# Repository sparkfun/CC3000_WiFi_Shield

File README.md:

CC3000_WiFi_Shield
====================

[  
*CC3000 WiFi Shield (WRL-12071)*](https://www.sparkfun.com/products/12071)

Arduino WiFi shield for the [TI CC3000 module](http://www.ti.com/product/cc3000). The datasheet can be found [here](http://www.ti.com/lit/ds/symlink/cc3000.pdf).

Arduino library and examples can be found in the [SFE_CC3000_Library](https://github.com/sparkfun/SFE_CC3000_Library).

This part was created in Eagle v6.5.0. Example sketches were created in Arduino v1.0.5.

Repository Contents
-------------------

* **/Hardware** - All Eagle design files (.brd, .sch, .STL)
* **/Production** - Test bed files and production panel files

Version History
---------------
* **v1.0** Initial release

License Information
-------------------
The hardware is released under [Creative Commons Share-alike 3.0](http://creativecommons.org/licenses/by-sa/3.0/).  
All other code is open source so please feel free to do anything you want with it; you buy me a beer if you use this and we meet someday ([Beerware license](http://en.wikipedia.org/wiki/Beerware)).

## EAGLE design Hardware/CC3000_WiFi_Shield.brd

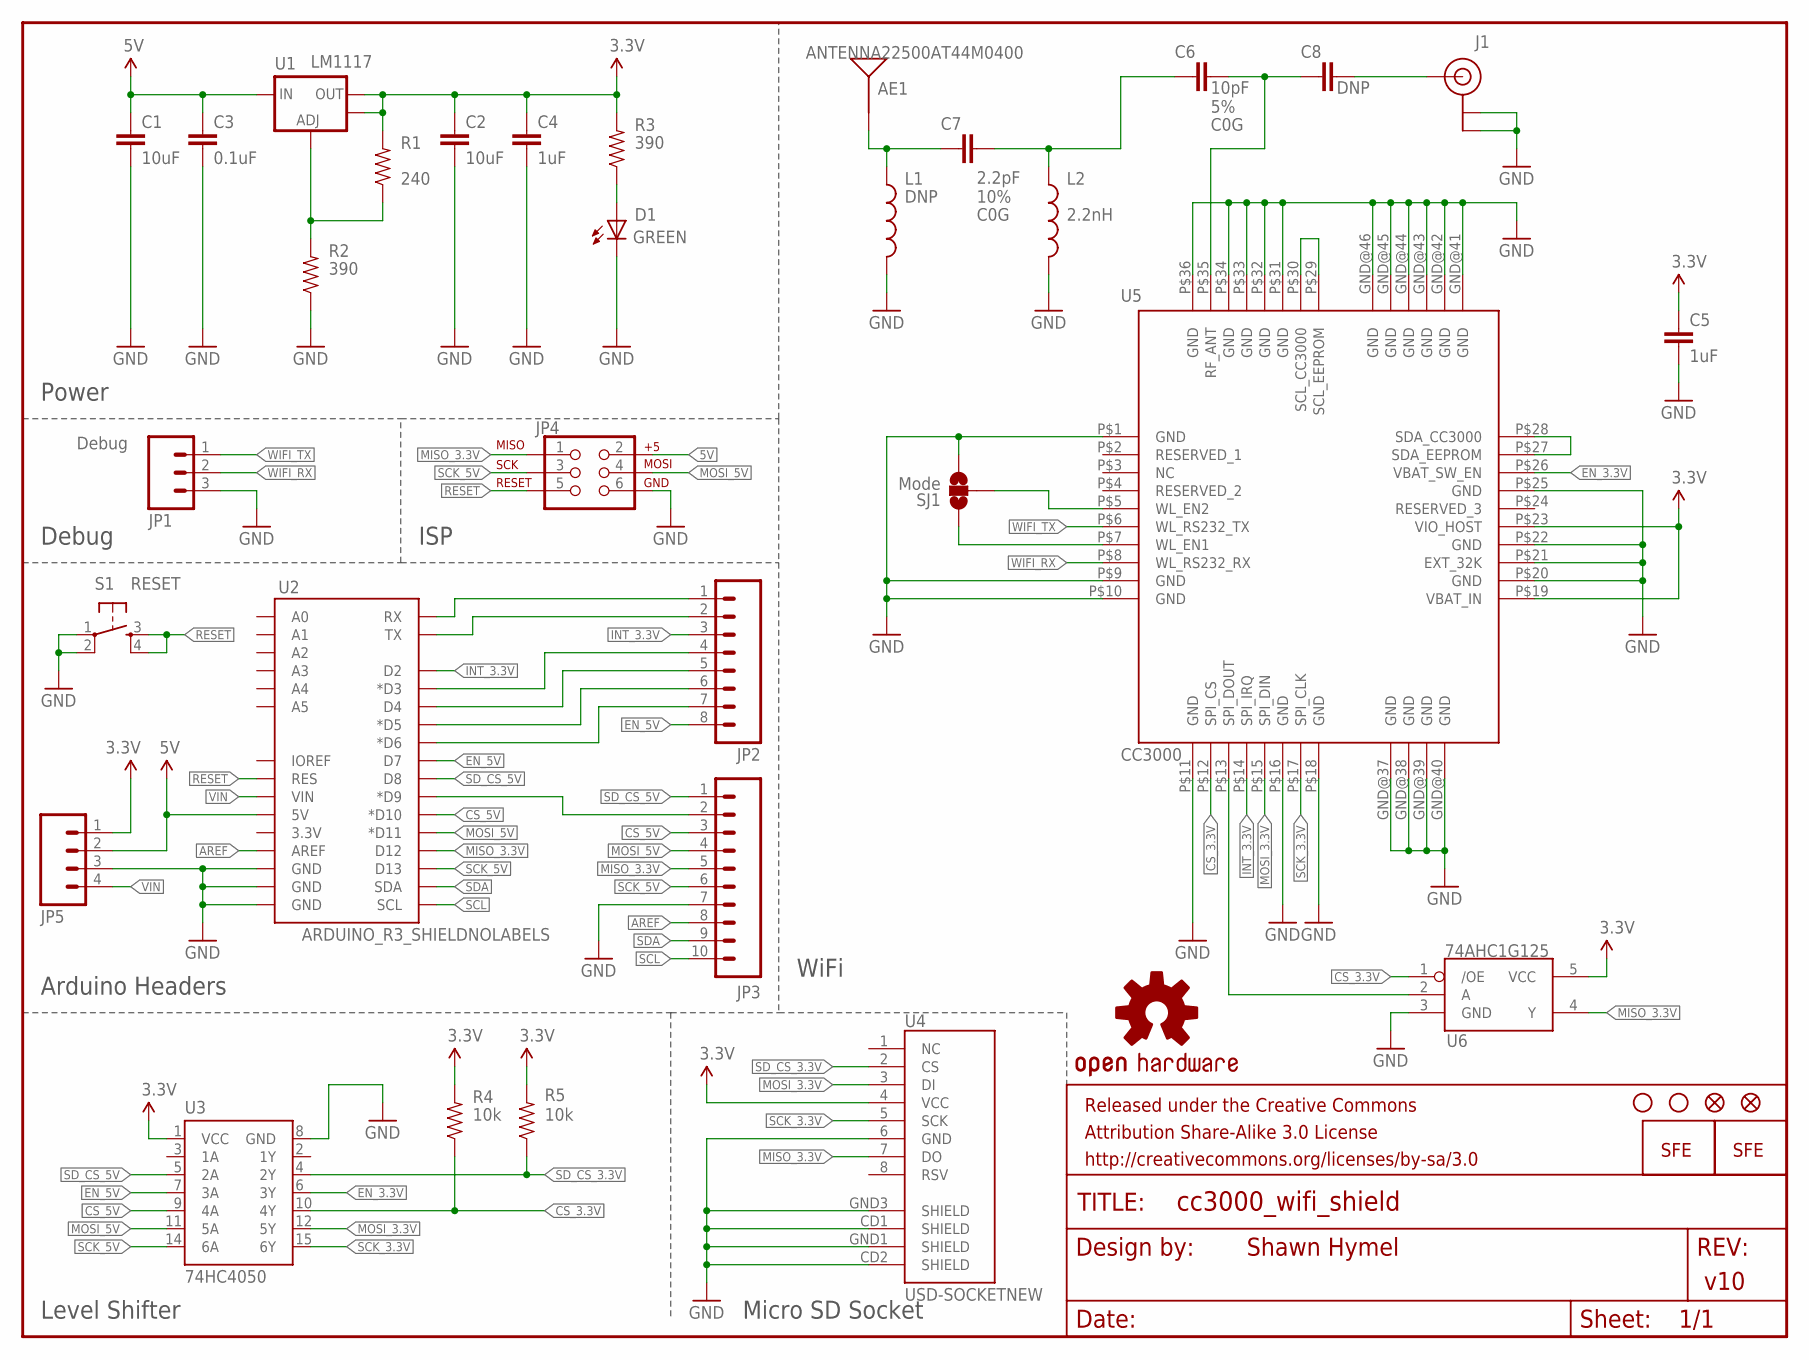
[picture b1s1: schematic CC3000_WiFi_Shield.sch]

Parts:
AE1: ANTENNA22500AT44M0400; ANTENNA-CHIP_2500AT44M0400
C1, C2: 10uF; 0805
C3: 0.1uF; 0603-CAP
C4, C5: 1uF; 0805
C6: 10pF; 0603-CAP
C7: 2.2pF; 0603-CAP
C8: DNP; 0603-CAP
D1: GREEN; LED-0603
FID1, FID2: FIDUCIAL1X2; FIDUCIAL-1X2
FRAME1: FRAME-LETTER; CREATIVE_COMMONS
J1: U.FL
JP1: Debug; 1X03
JP2: M08NO_SILK; 1X08_NO_SILK
JP3: M10NO_SILK; 1X10_NO_SILK
JP4: AVR_SPI_PRG_6PTH; 2X3
JP5: M04PTH; 1X04
L1: DNP; 0603
L2: 2.2nH; 0603
LOGO1: OSHW-LOGOS; OSHW-LOGO-S
LOGO2: LOGO-SFENEW; SFE-NEW-WEBLOGO
LOGO3: LOGO-SFESK; SFE-LOGO-FLAME
R1: 240; 0603-RES
R2, R3: 390; 0603-RES
R4, R5: 10k; 0603-RES
S1: RESET; TACTILE_SWITCH_SMD
SJ1: Mode; SJ_3_PASTE1&2
STANDOFF1, STANDOFF2: STAND-OFF
U1: LM1117; SOT223
U2: ARDUINO_R3_SHIELDNOLABELS; UNO_R3_SHIELD_NOLABELS
U3: 74HC4050; SO016
U4: USD-SOCKETNEW; MICRO-SD-SOCKET-PP
U5: CC3000; QFN-46_CC3000
U6: 74AHC1G125; SOT23-5

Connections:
3.3V: C2.1, C4.1, C5.1, JP5.1, R1.2, R3.2, R4.2, R5.2, U1.2 (OUT), U1.4 (OUT), U3.1 (VCC), U4.4 (VCC), U5.P$19 (VBAT_IN), U5.P$23 (VIO_HOST), U6.5 (VCC)
5V: C1.1, C3.1, JP4.2, JP5.2, U1.3 (IN), U2.5V
AREF: JP3.8, U2.AREF
CS_3.3V: R4.1, U3.10 (4Y), U5.P$12 (SPI_CS), U6.1 (/OE)
CS_5V: JP3.3, U2.D10 (*D10), U3.9 (4A)
EN_3.3V: U3.6 (3Y), U5.P$26 (VBAT_SW_EN)
EN_5V: JP2.8, U2.D7, U3.7 (3A)
GND: C1.2, C2.2, C3.2, C4.2, C5.2, D1.C, J1.P$1 (GND), J1.P$2 (GND), JP1.3, JP3.7, JP4.6, JP5.3, L1.2, L2.2, R2.1, S1.1, S1.2, SJ1.3, U2.GND@0 (GND), U2.GND@1 (GND), U2.GND@2 (GND), U3.8 (GND), U4.6 (GND), U4.CD1 (SHIELD), U4.CD2 (SHIELD), U4.GND1 (SHIELD), U4.GND3 (SHIELD), U5.GND@37 (GND), U5.GND@38 (GND), U5.GND@39 (GND), U5.GND@40 (GND), U5.GND@41 (GND), U5.GND@42 (GND), U5.GND@43 (GND), U5.GND@44 (GND), U5.GND@45 (GND), U5.GND@46 (GND), U5.P$1 (GND), U5.P$9 (GND), U5.P$10 (GND), U5.P$11 (GND), U5.P$16 (GND), U5.P$18 (GND), U5.P$20 (GND), U5.P$21 (EXT_32K), U5.P$22 (GND), U5.P$25 (GND), U5.P$31 (GND), U5.P$32 (GND), U5.P$33 (GND), U5.P$34 (GND), U5.P$36 (GND), U6.3 (GND)
INT_3.3V: JP2.3, U2.D2, U5.P$14 (SPI_IRQ)
MISO_3.3V: JP3.5, JP4.1, U2.D12, U4.7 (DO), U6.4 (Y)
MOSI_3.3V: U3.12 (5Y), U4.3 (DI), U5.P$15 (SPI_DIN)
MOSI_5V: JP3.4, JP4.4, U2.D11 (*D11), U3.11 (5A)
unnamed: R1.1, R2.2, U1.1 (ADJ)
unnamed: SJ1.2, U5.P$5 (WL_EN2)
unnamed: SJ1.1, U5.P$7 (WL_EN1)
unnamed: C6.1, C7.2, L2.1
unnamed: U5.P$27 (SDA_EEPROM), U5.P$28 (SDA_CC3000)
unnamed: U5.P$29 (SCL_EEPROM), U5.P$30 (SCL_CC3000)
unnamed: C6.2, C8.1, U5.P$35 (RF_ANT)
unnamed: C8.2, J1.P$3 (SIGNAL)
unnamed: AE1.FEED, C7.1, L1.1
unnamed: D1.A, R3.1
unnamed: JP2.1, U2.RX
unnamed: JP2.2, U2.TX
unnamed: JP2.4, U2.D3 (*D3)
unnamed: JP2.6, U2.D5 (*D5)
unnamed: JP2.7, U2.D6 (*D6)
unnamed: JP2.5, U2.D4
unnamed: JP3.2, U2.D9 (*D9)
RESET: JP4.5, S1.3, S1.4, U2.RES
SCK_3.3V: U3.15 (6Y), U4.5 (SCK), U5.P$17 (SPI_CLK)
SCK_5V: JP3.6, JP4.3, U2.D13, U3.14 (6A)
SCL: JP3.10, U2.SCL
SDA: JP3.9, U2.SDA
SD_CS_3.3V: R5.1, U3.4 (2Y), U4.2 (CS)
SD_CS_5V: JP3.1, U2.D8, U3.5 (2A)
VIN: JP5.4, U2.VIN
WIFI_MISO: U5.P$13 (SPI_DOUT), U6.2 (A)
WIFI_RX: JP1.2, U5.P$8 (WL_RS232_RX)
WIFI_TX: JP1.1, U5.P$6 (WL_RS232_TX)

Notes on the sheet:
Shawn Hymel
v10
Power
Debug
Arduino Headers
Level Shifter
Micro SD Socket
WiFi
ISP

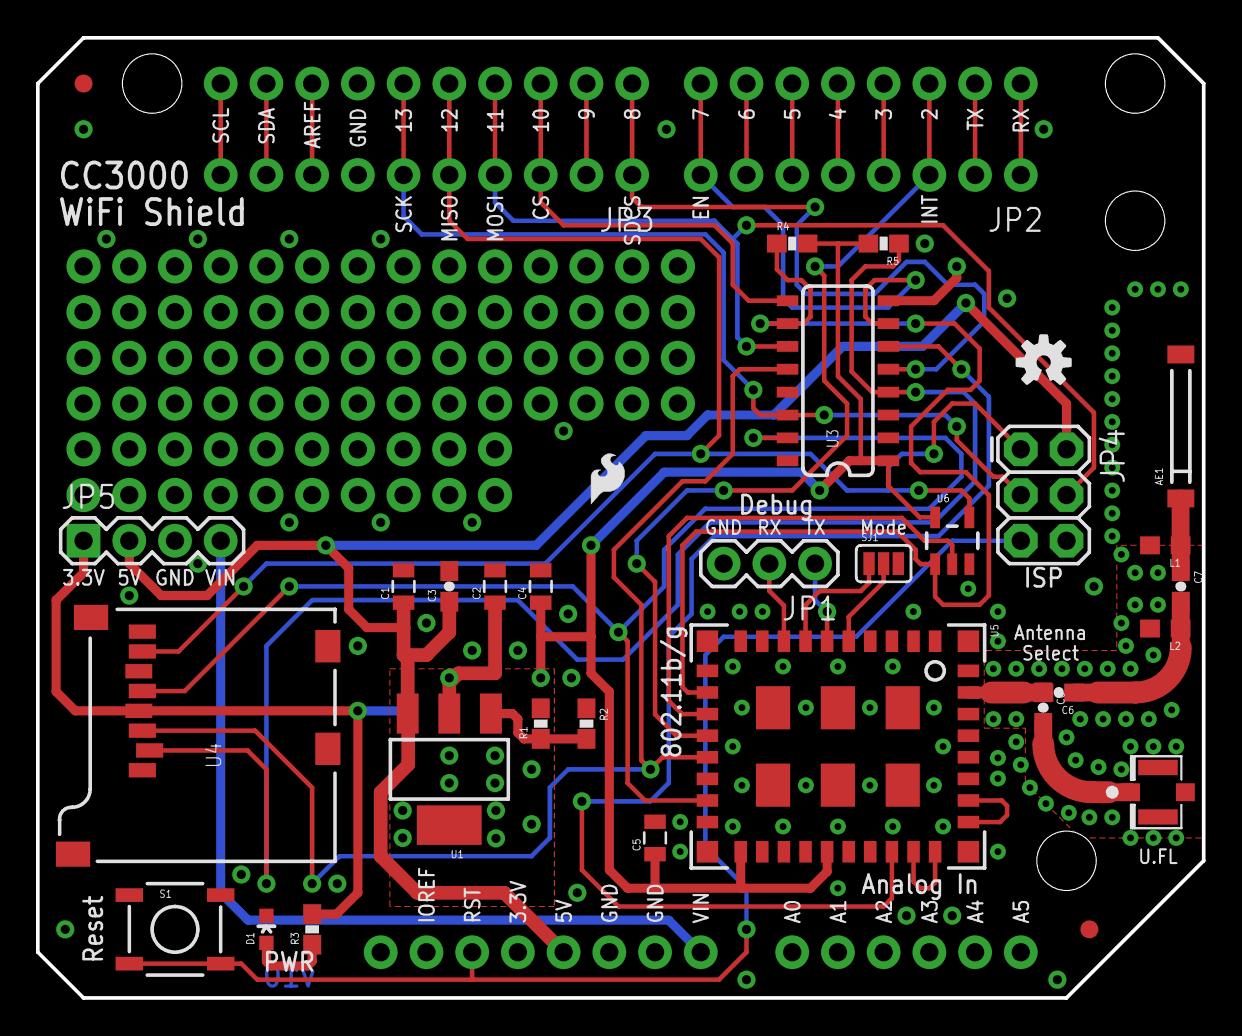
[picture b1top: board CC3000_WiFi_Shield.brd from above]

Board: 2 copper layers, 64.8 x 53.3 mm, 39 parts (1 on the bottom side), 40 nets.

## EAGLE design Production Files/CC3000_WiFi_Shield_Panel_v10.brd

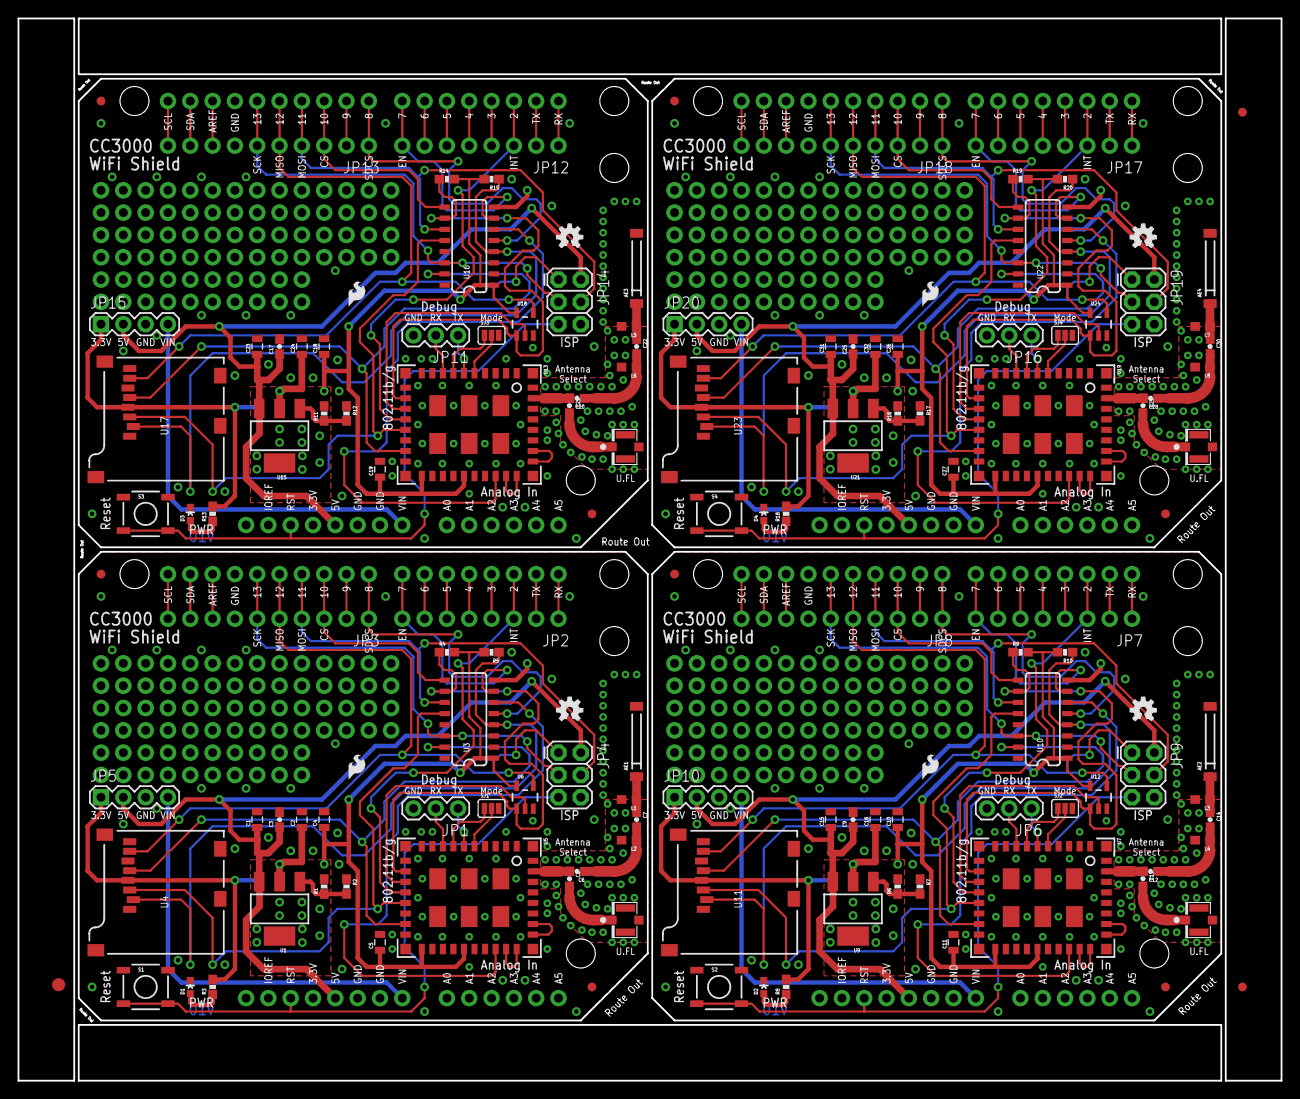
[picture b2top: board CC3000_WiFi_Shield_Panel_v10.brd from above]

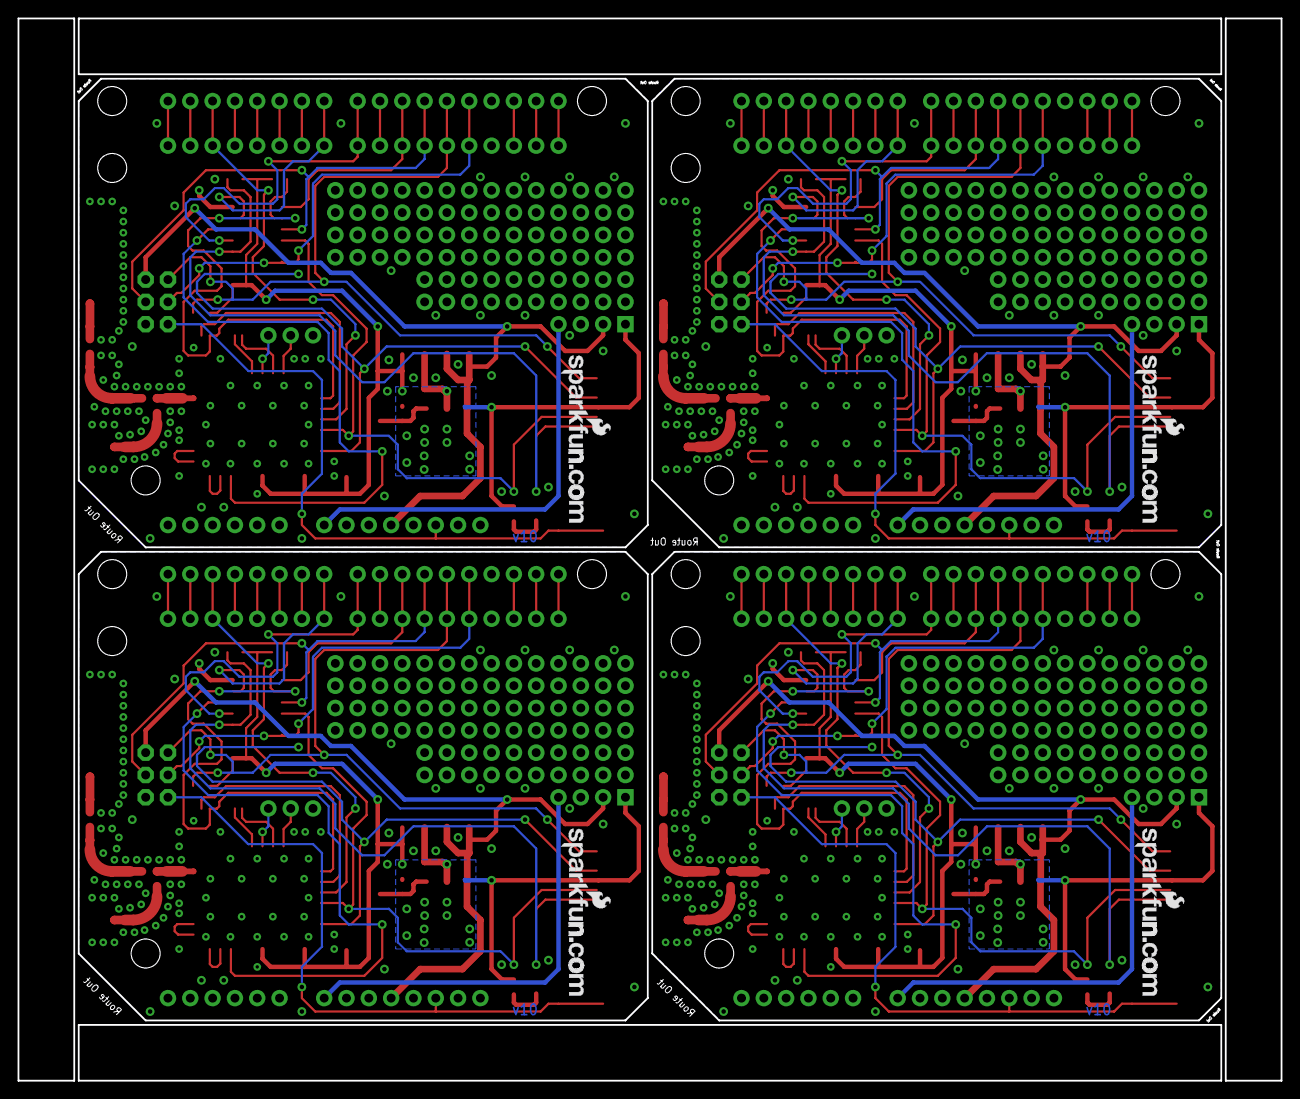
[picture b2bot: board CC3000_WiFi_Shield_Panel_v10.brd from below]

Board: 2 copper layers, 143.8 x 120.9 mm, 155 parts (4 on the bottom side), 160 nets.

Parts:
AE1, AE2, AE3, AE4: ANTENNA22500AT44M0400; ANTENNA-CHIP_2500AT44M0400
C1, C2, C15, C16, C23, C24, C31, C32: 10uF; 0805
C3, C9, C17, C25: 0.1uF; 0603-CAP
C4, C5, C10, C11, C18, C19, C26, C27: 1uF; 0805
C6, C12, C20, C28: 10pF; 0603-CAP
C7, C14, C22, C30: 2.2pF; 0603-CAP
C8, C13, C21, C29: DNP; 0603-CAP
D1, D2, D3, D4: GREEN; LED-0603
E$1: FIDUCIAL-1.5X3
E$4, E$5: FIDUCIAL-1X2
FID1, FID2, FID3, FID4, FID5, FID6, FID7, FID8: FIDUCIAL1X2; FIDUCIAL-1X2
J1, J2, J3, J4: U.FL
JP1, JP6, JP11, JP16: Debug; 1X03
JP2, JP7, JP12, JP17: 1X08_NO_SILK
JP3, JP8, JP13, JP18: M10NO_SILK; 1X10_NO_SILK
JP4, JP9, JP14, JP19: AVR_SPI_PRG_6PTH; 2X3
JP5, JP10, JP15, JP20: 1X04
L1, L3, L5, L7: DNP; 0603
L2, L4, L6, L8: 2.2nH; 0603
LOGO1, LOGO4, LOGO7, LOGO10: OSHW-LOGOS; OSHW-LOGO-S
LOGO2, LOGO5, LOGO8, LOGO11: LOGO-SFENEW; SFE-NEW-WEBLOGO
LOGO3, LOGO6, LOGO9, LOGO12: LOGO-SFESK; SFE-LOGO-FLAME
R1, R6, R11, R16: 240; 0603-RES
R2, R3, R7, R8, R12, R13, R17, R18: 390; 0603-RES
R4, R5, R9, R10, R14, R15, R19, R20: 10k; 0603-RES
S1, S2, S3, S4: RESET; TACTILE_SWITCH_SMD
SJ1, SJ2, SJ3, SJ4: Mode; SJ_3_PASTE1&2
STANDOFF1, STANDOFF2, STANDOFF3, STANDOFF4, STANDOFF5, STANDOFF6, STANDOFF7, STANDOFF8: STAND-OFF
U1, U9, U15, U21: LM1117; SOT223
U2, U8, U14, U20: ARDUINO_R3_SHIELDNOLABELS; UNO_R3_SHIELD_NOLABELS
U3, U10, U16, U22: 74HC4050; SO016
U4, U11, U17, U23: USD-SOCKETNEW; MICRO-SD-SOCKET-PP
U5, U7, U13, U19: CC3000; QFN-46_CC3000
U6, U12, U18, U24: 74AHC1G125; SOT23-5

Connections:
3.3V: C2.1, C4.1, C5.1, JP5.1, R1.2, R3.2, R4.2, R5.2, U1.2, U1.4, U3.1, U4.4, U5.P$19, U5.P$23, U6.5
3.3V1: C10.1, C11.1, C16.1, JP10.1, R6.2, R8.2, R9.2, R10.2, U7.P$19, U7.P$23, U9.2, U9.4, U10.1, U11.4, U12.5
3.3V2: C18.1, C19.1, C24.1, JP15.1, R11.2, R13.2, R14.2, R15.2, U13.P$19, U13.P$23, U15.2, U15.4, U16.1, U17.4, U18.5
3.3V3: C26.1, C27.1, C32.1, JP20.1, R16.2, R18.2, R19.2, R20.2, U19.P$19, U19.P$23, U21.2, U21.4, U22.1, U23.4, U24.5
5V: C1.1, C3.1, JP4.2, JP5.2, U1.3, U2.5V
5V1: C9.1, C15.1, JP9.2, JP10.2, U8.5V, U9.3
5V2: C17.1, C23.1, JP14.2, JP15.2, U14.5V, U15.3
5V3: C25.1, C31.1, JP19.2, JP20.2, U20.5V, U21.3
AREF: JP3.8, U2.AREF
AREF1: JP8.8, U8.AREF
AREF2: JP13.8, U14.AREF
AREF3: JP18.8, U20.AREF
CS_3.3V: R4.1, U3.10, U5.P$12, U6.1
CS_3.3V1: R9.1, U7.P$12, U10.10, U12.1
CS_3.3V2: R14.1, U13.P$12, U16.10, U18.1
CS_3.3V3: R19.1, U19.P$12, U22.10, U24.1
CS_5V: JP3.3, U2.D10, U3.9
CS_5V1: JP8.3, U8.D10, U10.9
CS_5V2: JP13.3, U14.D10, U16.9
CS_5V3: JP18.3, U20.D10, U22.9
EN_3.3V: U3.6, U5.P$26
EN_3.3V1: U7.P$26, U10.6
EN_3.3V2: U13.P$26, U16.6
EN_3.3V3: U19.P$26, U22.6
EN_5V: JP2.8, U2.D7, U3.7
EN_5V1: JP7.8, U8.D7, U10.7
EN_5V2: JP12.8, U14.D7, U16.7
EN_5V3: JP17.8, U20.D7, U22.7
GND: C1.2, C2.2, C3.2, C4.2, C5.2, D1.C, J1.P$1, J1.P$2, JP1.3, JP3.7, JP4.6, JP5.3, L1.2, L2.2, R2.1, S1.1, S1.2, SJ1.3, U2.GND@0, U2.GND@1, U2.GND@2, U3.8, U4.6, U4.CD1, U4.CD2, U4.GND1, U4.GND3, U5.GND@37, U5.GND@38, U5.GND@39, U5.GND@40, U5.GND@41, U5.GND@42, U5.GND@43, U5.GND@44, U5.GND@45, U5.GND@46, U5.P$1, U5.P$9, U5.P$10, U5.P$11, U5.P$16, U5.P$18, U5.P$20, U5.P$21, U5.P$22, U5.P$25, U5.P$31, U5.P$32, U5.P$33, U5.P$34, U5.P$36, U6.3
GND1: C9.2, C10.2, C11.2, C15.2, C16.2, D2.C, J2.P$1, J2.P$2, JP6.3, JP8.7, JP9.6, JP10.3, L3.2, L4.2, R7.1, S2.1, S2.2, SJ2.3, U7.GND@37, U7.GND@38, U7.GND@39, U7.GND@40, U7.GND@41, U7.GND@42, U7.GND@43, U7.GND@44, U7.GND@45, U7.GND@46, U7.P$1, U7.P$9, U7.P$10, U7.P$11, U7.P$16, U7.P$18, U7.P$20, U7.P$21, U7.P$22, U7.P$25, U7.P$31, U7.P$32, U7.P$33, U7.P$34, U7.P$36, U8.GND@0, U8.GND@1, U8.GND@2, U10.8, U11.6, U11.CD1, U11.CD2, U11.GND1, U11.GND3, U12.3
GND2: C17.2, C18.2, C19.2, C23.2, C24.2, D3.C, J3.P$1, J3.P$2, JP11.3, JP13.7, JP14.6, JP15.3, L5.2, L6.2, R12.1, S3.1, S3.2, SJ3.3, U13.GND@37, U13.GND@38, U13.GND@39, U13.GND@40, U13.GND@41, U13.GND@42, U13.GND@43, U13.GND@44, U13.GND@45, U13.GND@46, U13.P$1, U13.P$9, U13.P$10, U13.P$11, U13.P$16, U13.P$18, U13.P$20, U13.P$21, U13.P$22, U13.P$25, U13.P$31, U13.P$32, U13.P$33, U13.P$34, U13.P$36, U14.GND@0, U14.GND@1, U14.GND@2, U16.8, U17.6, U17.CD1, U17.CD2, U17.GND1, U17.GND3, U18.3
GND3: C25.2, C26.2, C27.2, C31.2, C32.2, D4.C, J4.P$1, J4.P$2, JP16.3, JP18.7, JP19.6, JP20.3, L7.2, L8.2, R17.1, S4.1, S4.2, SJ4.3, U19.GND@37, U19.GND@38, U19.GND@39, U19.GND@40, U19.GND@41, U19.GND@42, U19.GND@43, U19.GND@44, U19.GND@45, U19.GND@46, U19.P$1, U19.P$9, U19.P$10, U19.P$11, U19.P$16, U19.P$18, U19.P$20, U19.P$21, U19.P$22, U19.P$25, U19.P$31, U19.P$32, U19.P$33, U19.P$34, U19.P$36, U20.GND@0, U20.GND@1, U20.GND@2, U22.8, U23.6, U23.CD1, U23.CD2, U23.GND1, U23.GND3, U24.3
INT_3.3V: JP2.3, U2.D2, U5.P$14
INT_3.3V1: JP7.3, U7.P$14, U8.D2
INT_3.3V2: JP12.3, U13.P$14, U14.D2
INT_3.3V3: JP17.3, U19.P$14, U20.D2
MISO_3.3V: JP3.5, JP4.1, U2.D12, U4.7, U6.4
MISO_3.3V1: JP8.5, JP9.1, U8.D12, U11.7, U12.4
MISO_3.3V2: JP13.5, JP14.1, U14.D12, U17.7, U18.4
MISO_3.3V3: JP18.5, JP19.1, U20.D12, U23.7, U24.4
MOSI_3.3V: U3.12, U4.3, U5.P$15
MOSI_3.3V1: U7.P$15, U10.12, U11.3
MOSI_3.3V2: U13.P$15, U16.12, U17.3
MOSI_3.3V3: U19.P$15, U22.12, U23.3
MOSI_5V: JP3.4, JP4.4, U2.D11, U3.11
MOSI_5V1: JP8.4, JP9.4, U8.D11, U10.11
MOSI_5V2: JP13.4, JP14.4, U14.D11, U16.11
MOSI_5V3: JP18.4, JP19.4, U20.D11, U22.11
unnamed: R6.1, R7.2, U9.1
unnamed: R1.1, R2.2, U1.1
unnamed: SJ1.2, U5.P$5
unnamed: SJ1.1, U5.P$7
unnamed: C6.1, C7.2, L2.1
unnamed: U5.P$27, U5.P$28
unnamed: U5.P$29, U5.P$30
unnamed: C6.2, C8.1, U5.P$35
unnamed: C8.2, J1.P$3
unnamed: AE1.FEED, C7.1, L1.1
unnamed: D1.A, R3.1
unnamed: SJ2.2, U7.P$5
unnamed: SJ2.1, U7.P$7
unnamed: U7.P$27, U7.P$28
unnamed: U7.P$29, U7.P$30
unnamed: C12.1, C14.2, L4.1
unnamed: AE2.FEED, C14.1, L3.1
unnamed: C13.2, J2.P$3
unnamed: D2.A, R8.1
unnamed: JP2.1, U2.RX
unnamed: JP2.2, U2.TX
unnamed: JP2.4, U2.D3
unnamed: JP2.6, U2.D5
unnamed: JP2.7, U2.D6
unnamed: JP2.5, U2.D4
unnamed: JP3.2, U2.D9
unnamed: C12.2, C13.1, U7.P$35
unnamed: JP7.4, U8.D3
unnamed: JP7.6, U8.D5
unnamed: JP7.7, U8.D6
unnamed: JP7.1, U8.RX
unnamed: JP7.2, U8.TX
unnamed: JP8.2, U8.D9
unnamed: JP7.5, U8.D4
unnamed: R11.1, R12.2, U15.1
unnamed: SJ3.2, U13.P$5
unnamed: SJ3.1, U13.P$7
unnamed: U13.P$27, U13.P$28
unnamed: U13.P$29, U13.P$30
unnamed: C20.1, C22.2, L6.1
unnamed: AE3.FEED, C22.1, L5.1
unnamed: C21.2, J3.P$3
unnamed: D3.A, R13.1
unnamed: C20.2, C21.1, U13.P$35
unnamed: JP12.4, U14.D3
unnamed: JP12.6, U14.D5
unnamed: JP12.7, U14.D6
unnamed: JP12.1, U14.RX
unnamed: JP12.2, U14.TX
unnamed: JP13.2, U14.D9
unnamed: JP12.5, U14.D4
unnamed: R16.1, R17.2, U21.1
unnamed: SJ4.2, U19.P$5
unnamed: SJ4.1, U19.P$7
unnamed: U19.P$27, U19.P$28
unnamed: U19.P$29, U19.P$30
unnamed: C28.1, C30.2, L8.1
unnamed: AE4.FEED, C30.1, L7.1
unnamed: C29.2, J4.P$3
unnamed: D4.A, R18.1
unnamed: C28.2, C29.1, U19.P$35
unnamed: JP17.4, U20.D3
unnamed: JP17.6, U20.D5
unnamed: JP17.7, U20.D6
unnamed: JP17.1, U20.RX
unnamed: JP17.2, U20.TX
unnamed: JP18.2, U20.D9
unnamed: JP17.5, U20.D4
RESET: JP4.5, S1.3, S1.4, U2.RES
RESET1: JP9.5, S2.3, S2.4, U8.RES
RESET2: JP14.5, S3.3, S3.4, U14.RES
RESET3: JP19.5, S4.3, S4.4, U20.RES
SCK_3.3V: U3.15, U4.5, U5.P$17
SCK_3.3V1: U7.P$17, U10.15, U11.5
SCK_3.3V2: U13.P$17, U16.15, U17.5
SCK_3.3V3: U19.P$17, U22.15, U23.5
SCK_5V: JP3.6, JP4.3, U2.D13, U3.14
SCK_5V1: JP8.6, JP9.3, U8.D13, U10.14
SCK_5V2: JP13.6, JP14.3, U14.D13, U16.14
SCK_5V3: JP18.6, JP19.3, U20.D13, U22.14
SCL: JP3.10, U2.SCL
SCL1: JP8.10, U8.SCL
SCL2: JP13.10, U14.SCL
SCL3: JP18.10, U20.SCL
SDA: JP3.9, U2.SDA
SDA1: JP8.9, U8.SDA
SDA2: JP13.9, U14.SDA
SDA3: JP18.9, U20.SDA
SD_CS_3.3V: R5.1, U3.4, U4.2
SD_CS_3.3V1: R10.1, U10.4, U11.2
SD_CS_3.3V2: R15.1, U16.4, U17.2
SD_CS_3.3V3: R20.1, U22.4, U23.2
SD_CS_5V: JP3.1, U2.D8, U3.5
SD_CS_5V1: JP8.1, U8.D8, U10.5
SD_CS_5V2: JP13.1, U14.D8, U16.5
SD_CS_5V3: JP18.1, U20.D8, U22.5
VIN: JP5.4, U2.VIN
VIN1: JP10.4, U8.VIN
VIN2: JP15.4, U14.VIN
VIN3: JP20.4, U20.VIN
WIFI_MISO: U5.P$13, U6.2
WIFI_MISO1: U7.P$13, U12.2
WIFI_MISO2: U13.P$13, U18.2
WIFI_MISO3: U19.P$13, U24.2
WIFI_RX: JP1.2, U5.P$8
WIFI_RX1: JP6.2, U7.P$8
WIFI_RX2: JP11.2, U13.P$8
WIFI_RX3: JP16.2, U19.P$8
WIFI_TX: JP1.1, U5.P$6
WIFI_TX1: JP6.1, U7.P$6
WIFI_TX2: JP11.1, U13.P$6
WIFI_TX3: JP16.1, U19.P$6

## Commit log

2013-09-16 Component placement on board complete
2013-09-17 Prototype board ready for review
2013-09-19 Fixed floating 3.3V paddle on LM317. Made stitching vias near RF section 10 mils.
2013-09-19 Changed stitching via size to 15 mils
2013-09-23 Ready for prototype.
2013-12-11 Added high-Z protection on MISO, replaced tantalums, added 2nd set of headers on shield
2013-12-12 Made corrections to schematic/board from first prototype
2013-12-12 Board ready for review (second round of prototypes)
2013-12-17 Added power breakout near proto area. Removed silk from shield headers. Changed silk text to 0.032 in. size. Added ISP headers to work with Leonardo. Added 10-pin shield headers to work woth UNO R3. 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
2014-01-16 Moved ext antenna mount back 50 mil; re-routed SD_CS line to avoid splitting power plane on bottom; Added 'Antenna Select' to SS; Added SS marker to U.FL; Added 'Mode' in SS to jumper; Changed to v10
2014-01-23 Added silk U.FL; Adjusted tvalue markings for easier reading
2014-01-29 Created Panel
2014-03-18 Added pdf of schematic
2014-04-03 Updated readme to include product information.

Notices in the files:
parts and their libraries:
SparkFun-Aesthetics: Licensing: CC v3.0 Share-Alike You are welcome to use this library for commercial purposes.
SparkFun-Aesthetics: Released under the Creative Commons Attribution Share-Alike 3.0 License
SparkFun-Aesthetics: Released under the Creative Commons
